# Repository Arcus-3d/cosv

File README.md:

## COSV - Cam Open Source Ventilator.
Cam based ventilator designed to fit directly on an BVM, on the patient.

The [COSV - Cam Open Source Ventilator](https://hackaday.io/project/170507) project is open source hardware. 
This github repository hosts the [OpenSCAD](http://www.openscad.org) source and the rendered STL images for quick access.

Hardware designs (schematics and CAD) files are licensed under the [GNU GENERAL PUBLIC LICENSE Version 3](https://www.gnu.org/licenses/gpl-3.0.md) and follow the terms of the [OSHW (Open-source hardware) Statement of Principles 1.0.](http://freedomdefined.org/OSHW)

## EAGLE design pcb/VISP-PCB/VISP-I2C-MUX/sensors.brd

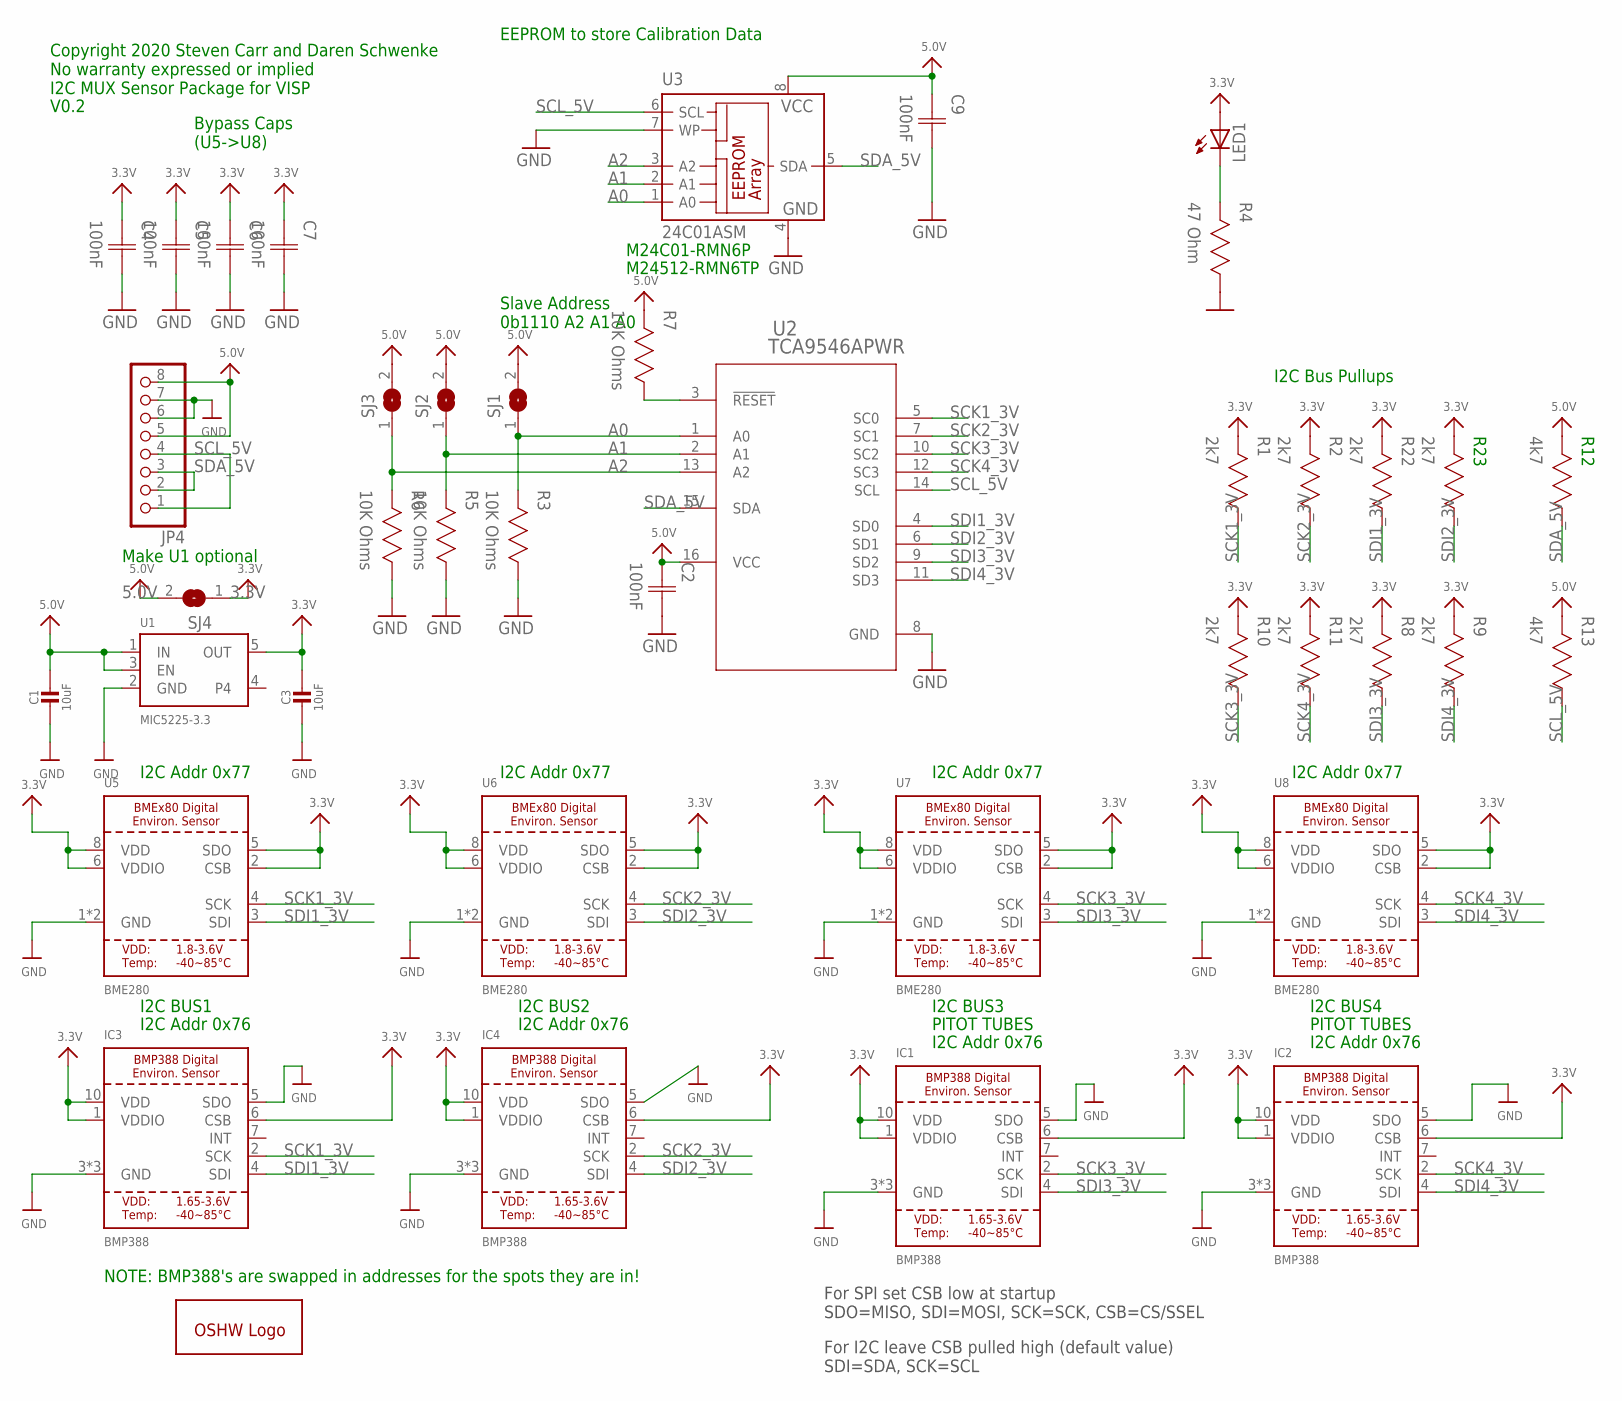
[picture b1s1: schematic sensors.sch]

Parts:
C1, C3: 10uF; _0805; MPN C1608X5R1A106M080AC
C2, C9: 100nF; CAP0402; MPN CL10B104KB8NNNC
C4, C5, C6, C7: 100nF; CAP0402; MPN CL10F104ZO8NNNC
GOLD_ORB_SM1: OSHWLOGOLOGO8MM; OSHW_8MM
IC1, IC2, IC3, IC4: BMP388; MPN BMP388
JP4: PINHD-1X08_2.54; 1X08
LED1: LEDCHIP-LED0603; CHIP-LED0603; MPN SML-D12P8WT86
R1, R2, R8, R9, R10, R11, R22, R23: 2k7; RES0402; MPN CRCW060310K0FKEAC
R3, R5, R6, R7: 10K Ohms; RES0402; MPN CRCW060310K0FKEAC
R4: 47 Ohm; RES0402; MPN RC0603FR-0747RL
R12, R13: 4k7; RES0402; MPN CRCW060310K0FKEAC
SJ1, SJ2, SJ3, SJ4: SJ
U1: MIC5225-3.3; SOT23-5; MPN MIC5225-3.3YM5-TR
U2: TCA9546APWR; PW16
U3: 24C01ASM; SO-08M; MPN M24C01-RMN6P
U5, U6, U7, U8: BME280

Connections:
3.3V: C3.1, C4.1 (C1), C5.1 (C1), C6.1 (C1), C7.1 (C1), IC1.1 (VDDIO), IC1.6 (CSB), IC1.10 (VDD), IC2.1 (VDDIO), IC2.6 (CSB), IC2.10 (VDD), IC3.1 (VDDIO), IC3.6 (CSB), IC3.10 (VDD), IC4.1 (VDDIO), IC4.6 (CSB), IC4.10 (VDD), LED1.A, R1.2, R2.2, R8.2, R9.2, R10.2, R11.2, R22.2, R23.2, SJ4.1, U1.5 (OUT), U5.2 (CSB), U5.5 (SDO), U5.6 (VDDIO), U5.8 (VDD), U6.2 (CSB), U6.5 (SDO), U6.6 (VDDIO), U6.8 (VDD), U7.2 (CSB), U7.5 (SDO), U7.6 (VDDIO), U7.8 (VDD), U8.2 (CSB), U8.5 (SDO), U8.6 (VDDIO), U8.8 (VDD)
5.0V: C1.1, C2.1 (C1), C9.1 (C1), JP4.5, JP4.8, R7.2, R12.2, R13.2, SJ1.2, SJ2.2, SJ3.2, SJ4.2, U1.1 (IN), U1.3 (EN), U2.16 (VCC), U3.8 (VCC)
A0: R3.2, SJ1.1, U2.1 (A0), U3.1 (A0)
A1: R5.2, SJ2.1, U2.2 (A1), U3.2 (A1)
A2: R6.2, SJ3.1, U2.13 (A2), U3.3 (A2)
GND: C1.2, C2.2 (C2), C3.2, C4.2 (C2), C5.2 (C2), C6.2 (C2), C7.2 (C2), C9.2 (C2), IC1.3 (GND), IC1.5 (SDO), IC1.8 (GND), IC1.9 (GND), IC2.3 (GND), IC2.5 (SDO), IC2.8 (GND), IC2.9 (GND), IC3.3 (GND), IC3.5 (SDO), IC3.8 (GND), IC3.9 (GND), IC4.3 (GND), IC4.5 (SDO), IC4.8 (GND), IC4.9 (GND), JP4.6, JP4.7, R3.1, R4.1, R5.1, R6.1, U1.2 (GND), U2.8 (GND), U3.4 (GND), U3.7 (WP), U5.1 (GND), U5.7 (GND), U6.1 (GND), U6.7 (GND), U7.1 (GND), U7.7 (GND), U8.1 (GND), U8.7 (GND)
LED: LED1.C, R4.2
RESET: R7.1, U2.3 (!RESET)
SCK1_3V: IC3.2 (SCK), R1.1, U2.5 (SC0), U5.4 (SCK)
SCK2_3V: IC4.2 (SCK), R2.1, U2.7 (SC1), U6.4 (SCK)
SCK3_3V: IC1.2 (SCK), R10.1, U2.10 (SC2), U7.4 (SCK)
SCK4_3V: IC2.2 (SCK), R11.1, U2.12 (SC3), U8.4 (SCK)
SCL_5V: JP4.1, JP4.4, R13.1, U2.14 (SCL), U3.6 (SCL)
SDA_5V: JP4.2, JP4.3, R12.1, U2.15 (SDA), U3.5 (SDA)
SDI1_3V: IC3.4 (SDI), R22.1, U2.4 (SD0), U5.3 (SDI)
SDI2_3V: IC4.4 (SDI), R23.1, U2.6 (SD1), U6.3 (SDI)
SDI3_3V: IC1.4 (SDI), R8.1, U2.9 (SD2), U7.3 (SDI)
SDI4_3V: IC2.4 (SDI), R9.1, U2.11 (SD3), U8.3 (SDI)

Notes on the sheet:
Bypass Caps (U5->U8)
Copyright 2020 Steven Carr and Daren Schwenke No warranty expressed or implied I2C MUX Sensor Package for VISP
EEPROM to store Calibration Data
V0.2
Make U1 optional
For SPI set CSB low at startup SDO=MISO, SDI=MOSI, SCK=SCK, CSB=CS/SSEL
For I2C leave CSB pulled high (default value) SDI=SDA, SCK=SCL
M24C01-RMN6P
M24512-RMN6TP
I2C Bus Pullups
Slave Address 0b1110 A2 A1 A0
I2C Addr 0x76
PITOT TUBES
I2C Addr 0x77
I2C BUS1
I2C BUS2
I2C BUS3
I2C BUS4
NOTE: BMP388's are swapped in addresses for the spots they are in!

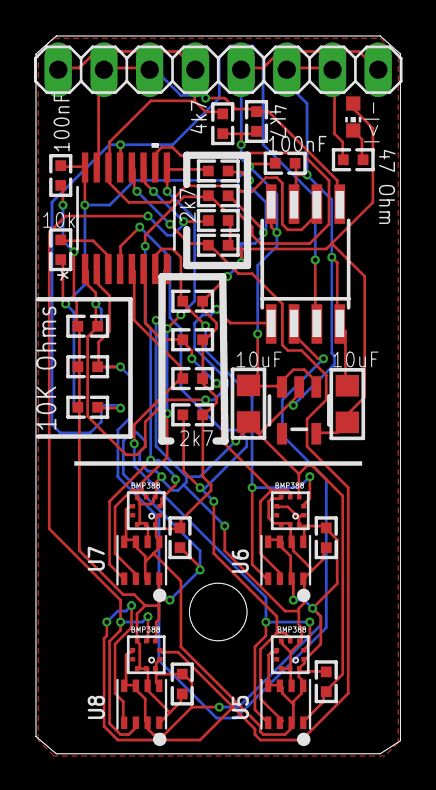
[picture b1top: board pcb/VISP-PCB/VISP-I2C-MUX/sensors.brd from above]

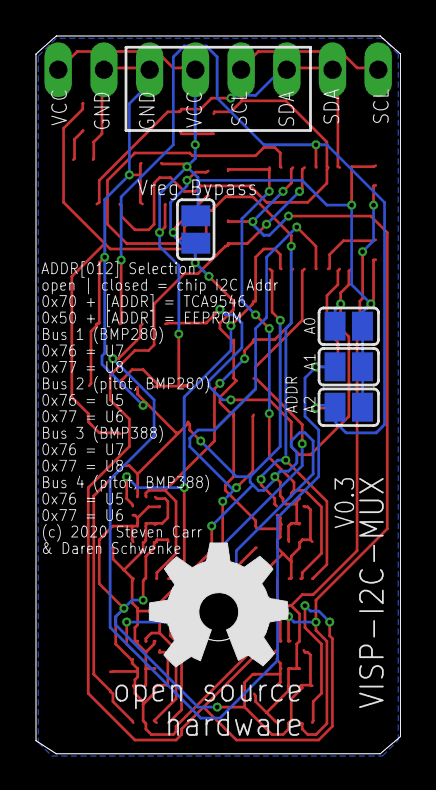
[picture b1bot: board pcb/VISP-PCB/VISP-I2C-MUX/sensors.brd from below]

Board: 2 copper layers, 20.2 x 39.9 mm, 41 parts (5 on the bottom side), 18 nets.

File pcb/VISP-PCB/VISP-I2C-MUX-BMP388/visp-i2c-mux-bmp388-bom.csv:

Item #,Qty,Ref Des,Manufacturer,Mfg Part #,Dist. Part #,Description,Package,Type
1,2,"C1,C3",Murata Electronics,GRM188R61A106KE69J ,490-14372-1-ND ,10uF ceramic capacitor,0805,SMT
2,6,"C2,C4,C5,C6,C7,C9",Murata Electronics, GRM155R71C104KA88J ,490-6328-1-ND ,100nF ceramic capacitor,0402,SMT
3,8,"R1,R2,R8,R9,R10,R11,R22,R23",TE Connectivity Passive Product,CRGCQ0402F2K7 ,A129632CT-ND ,2k7 resistor,0402,SMT
4,4,"R3,R5,R6,R7",TE Connectivity Passive Product,CRGCQ0402J10K ,A130054CT-ND ,10K resistor,0402,SMT
5,1,R4,TE Connectivity Passive Product,CRGCQ0402F47R , A129611CT-ND ,47 ohm resistor,0402,SMT
6,1,LED1,Rohm Semiconductor,SML-D12P8WT86,511-1579-1-ND ,LED GREEN DIFFUSED 0603 SMD ,0603,SMT
7,1,U1,Microchip Technology,MIC5225-3.3YM5-TR, 576-2980-1-ND ,IC REG LINEAR 3.3V 150MA SOT23-5 ,SOT23-5,SMT
8,1,U2,Texas Instruments,TCA9546APWR,296-40578-1-ND ,IC I2C SW 4CH W/RESET 16TSSOP ,16TSSOP,SMT
9,1,U3,Microchip Technology,AT24C512C-SSHD-T ,AT24C512C-SSHD-TCT-ND ,IC EEPROM 512K I2C 1MHZ 8SOIC ,SO-08M,SMT
10,4,"U5,U6,U7,U8",Bosch Sensortec,BMP388,828-1079-1-ND ,Barometric Pressure Sensor,BMP388,SMT
,,,,,,,,
,,,,,,,,
,,,,,,,,
Unique,10,,,,,,,
Total,29,,,,,,,
Thru Hole,0,,,,,,,
Has BGA,Yes,,,,,,,

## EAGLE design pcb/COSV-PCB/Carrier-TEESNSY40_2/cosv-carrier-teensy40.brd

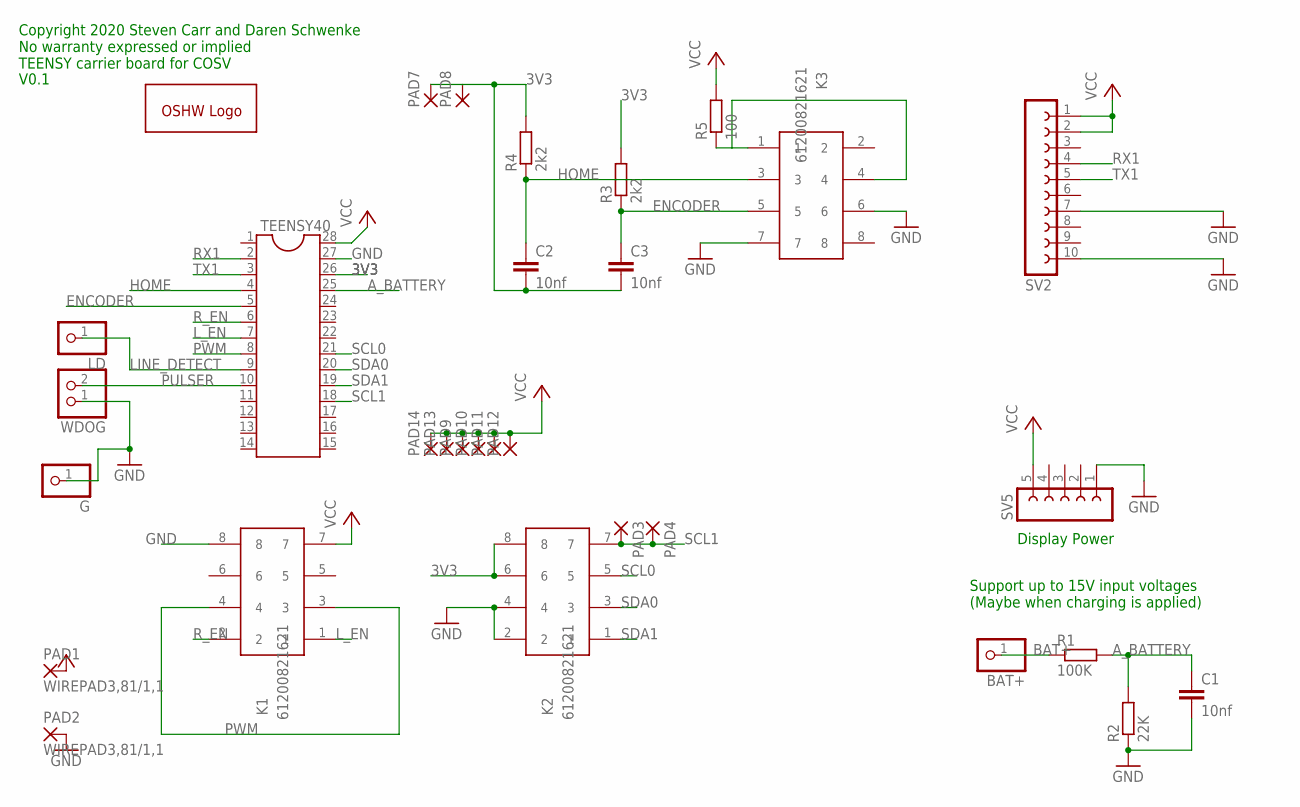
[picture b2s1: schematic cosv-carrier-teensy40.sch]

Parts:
BAT+: PINHD-1X01_2.54-S; 1X01-S
C1, C2, C3: 10nf; C1206
G: PINHD-1X01_2.54-S; 1X01-S
GOLD_ORB_SM1: OSHWLOGOLOGO8MM; OSHW_8MM
K1, K2, K3: 61200821621
LD: PINHD-1X01_2.54-S; 1X01-S
PAD1, PAD2: WIREPAD3,81/1,1; 3,81/1,1
PAD3, PAD4, PAD7, PAD8, PAD9, PAD10, PAD11, PAD12, PAD13, PAD14: 1,6/0,9
R1: 100K; R1206
R2: 22K; R1206
R3, R4: 2k2; R1206
R5: 100; R1206
SV2: FE10-1; FE10
SV5: FE05W
TEENSY40: DIL28; DIL28-6
WDOG: PINHD-1X2; 1X02

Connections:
3V3: C2.2, C3.2, K2.6, K2.8, PAD7.1, PAD8.1, R3.2, R4.2, TEENSY40.26
A_BATTERY: C1.1, R1.2, R2.2, TEENSY40.25
BAT+: BAT+.1, R1.1
ENCODER: C3.1, K3.5, R3.1, TEENSY40.5
GND: C1.2, G.1, K1.8, K2.2, K2.4, K3.6, K3.7, PAD2.1, R2.1, SV2.7, SV2.10, SV5.1, TEENSY40.27, WDOG.1
HOME: C2.1, K3.3, R4.1, TEENSY40.4
LED: K3.1, K3.4, R5.1
LINE_DETECT: LD.1, TEENSY40.9
L_EN: K1.1, TEENSY40.7
PULSER: TEENSY40.10, WDOG.2
PWM: K1.3, K1.4, TEENSY40.8
RX1: SV2.4, TEENSY40.2
R_EN: K1.2, TEENSY40.6
SCL0: K2.5, TEENSY40.21
SCL1: K2.7, PAD3.1, PAD4.1, TEENSY40.18
SDA0: K2.3, TEENSY40.20
SDA1: K2.1, TEENSY40.19
TX1: SV2.5, TEENSY40.3
VCC: K1.7, PAD1.1, PAD9.1, PAD10.1, PAD11.1, PAD12.1, PAD13.1, PAD14.1, R5.2, SV2.1, SV2.2, SV5.5, TEENSY40.28

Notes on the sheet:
Display Power
Support up to 15V input voltages (Maybe when charging is applied)
Copyright 2020 Steven Carr and Daren Schwenke No warranty expressed or implied TEENSY carrier board for COSV
V0.1

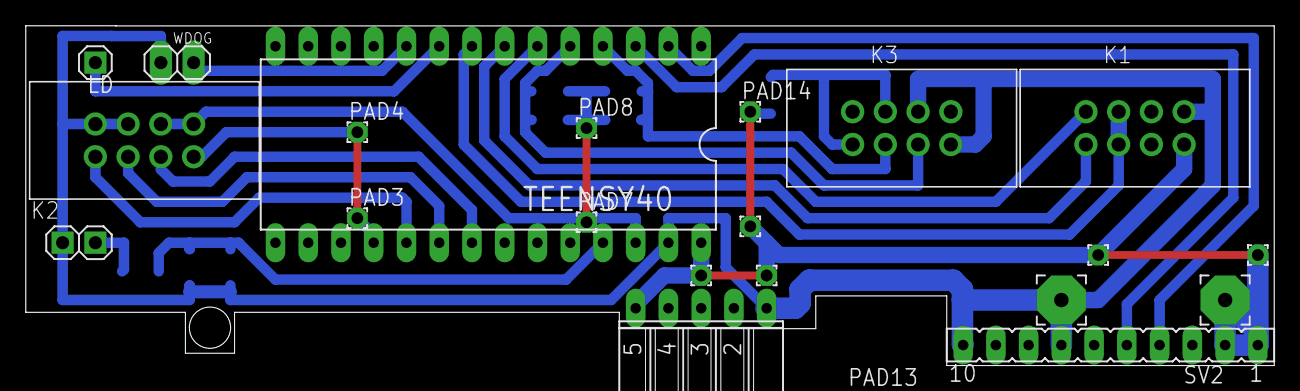
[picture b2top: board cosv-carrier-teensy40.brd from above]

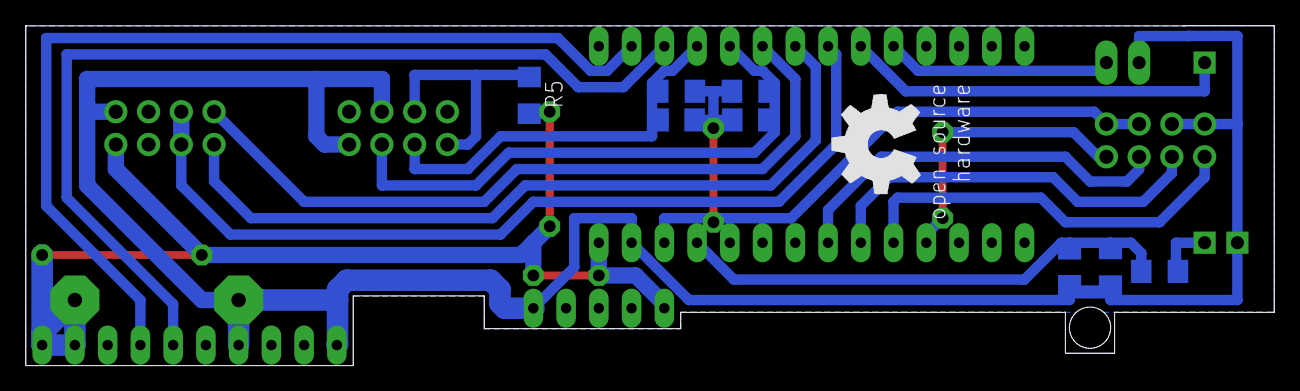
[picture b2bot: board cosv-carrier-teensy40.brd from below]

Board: 2 copper layers, 96.8 x 26.4 mm, 31 parts (9 on the bottom side), 19 nets.

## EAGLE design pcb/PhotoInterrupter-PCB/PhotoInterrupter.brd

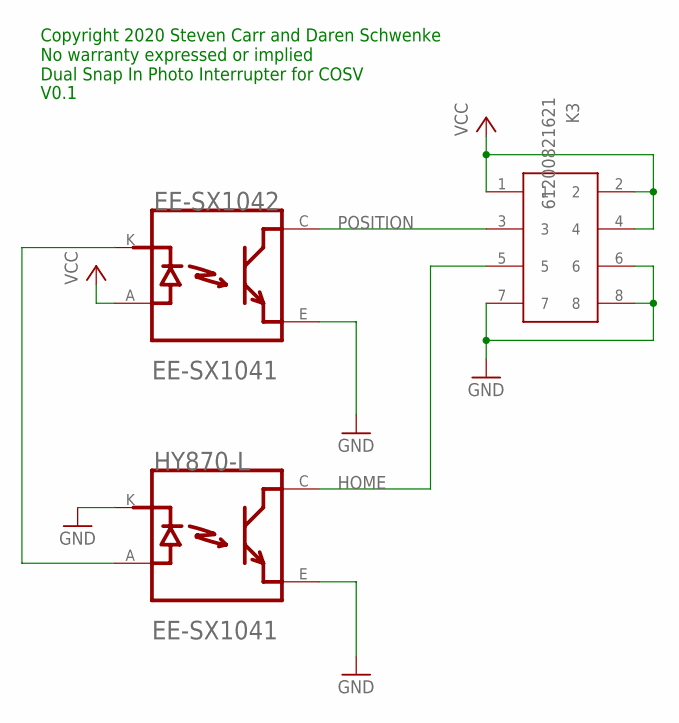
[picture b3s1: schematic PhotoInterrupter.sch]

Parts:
EE-SX1042: OMRON_ELECTRONICS_INC-EMC_DIV_EE-SX1041OMRON_ELEC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; OMRON_ELECTRONICS_INC-EMC_DIV_EE-SX1041_0
HY870-L: OMRON_ELECTRONICS_INC-EMC_DIV_EE-SX1041OMRON_ELEC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; OMRON_ELECTRONICS_INC-EMC_DIV_EE-SX1041_0
K3: 61200821621

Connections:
GND: EE-SX1042.E, HY870-L.E, HY870-L.K, K3.6, K3.7, K3.8
HOME: HY870-L.C, K3.5
unnamed: EE-SX1042.K, HY870-L.A
POSITION: EE-SX1042.C, K3.3
VCC: EE-SX1042.A, K3.1, K3.2, K3.4

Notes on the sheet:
Copyright 2020 Steven Carr and Daren Schwenke No warranty expressed or implied Dual Snap In Photo Interrupter for COSV
V0.1

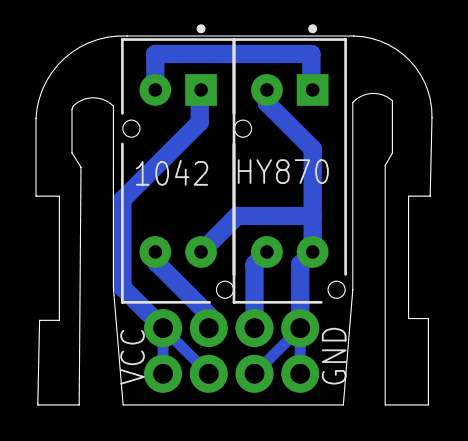
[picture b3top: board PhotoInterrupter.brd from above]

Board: 2 copper layers, 22.0 x 20.5 mm, 3 parts (1 on the bottom side), 5 nets.

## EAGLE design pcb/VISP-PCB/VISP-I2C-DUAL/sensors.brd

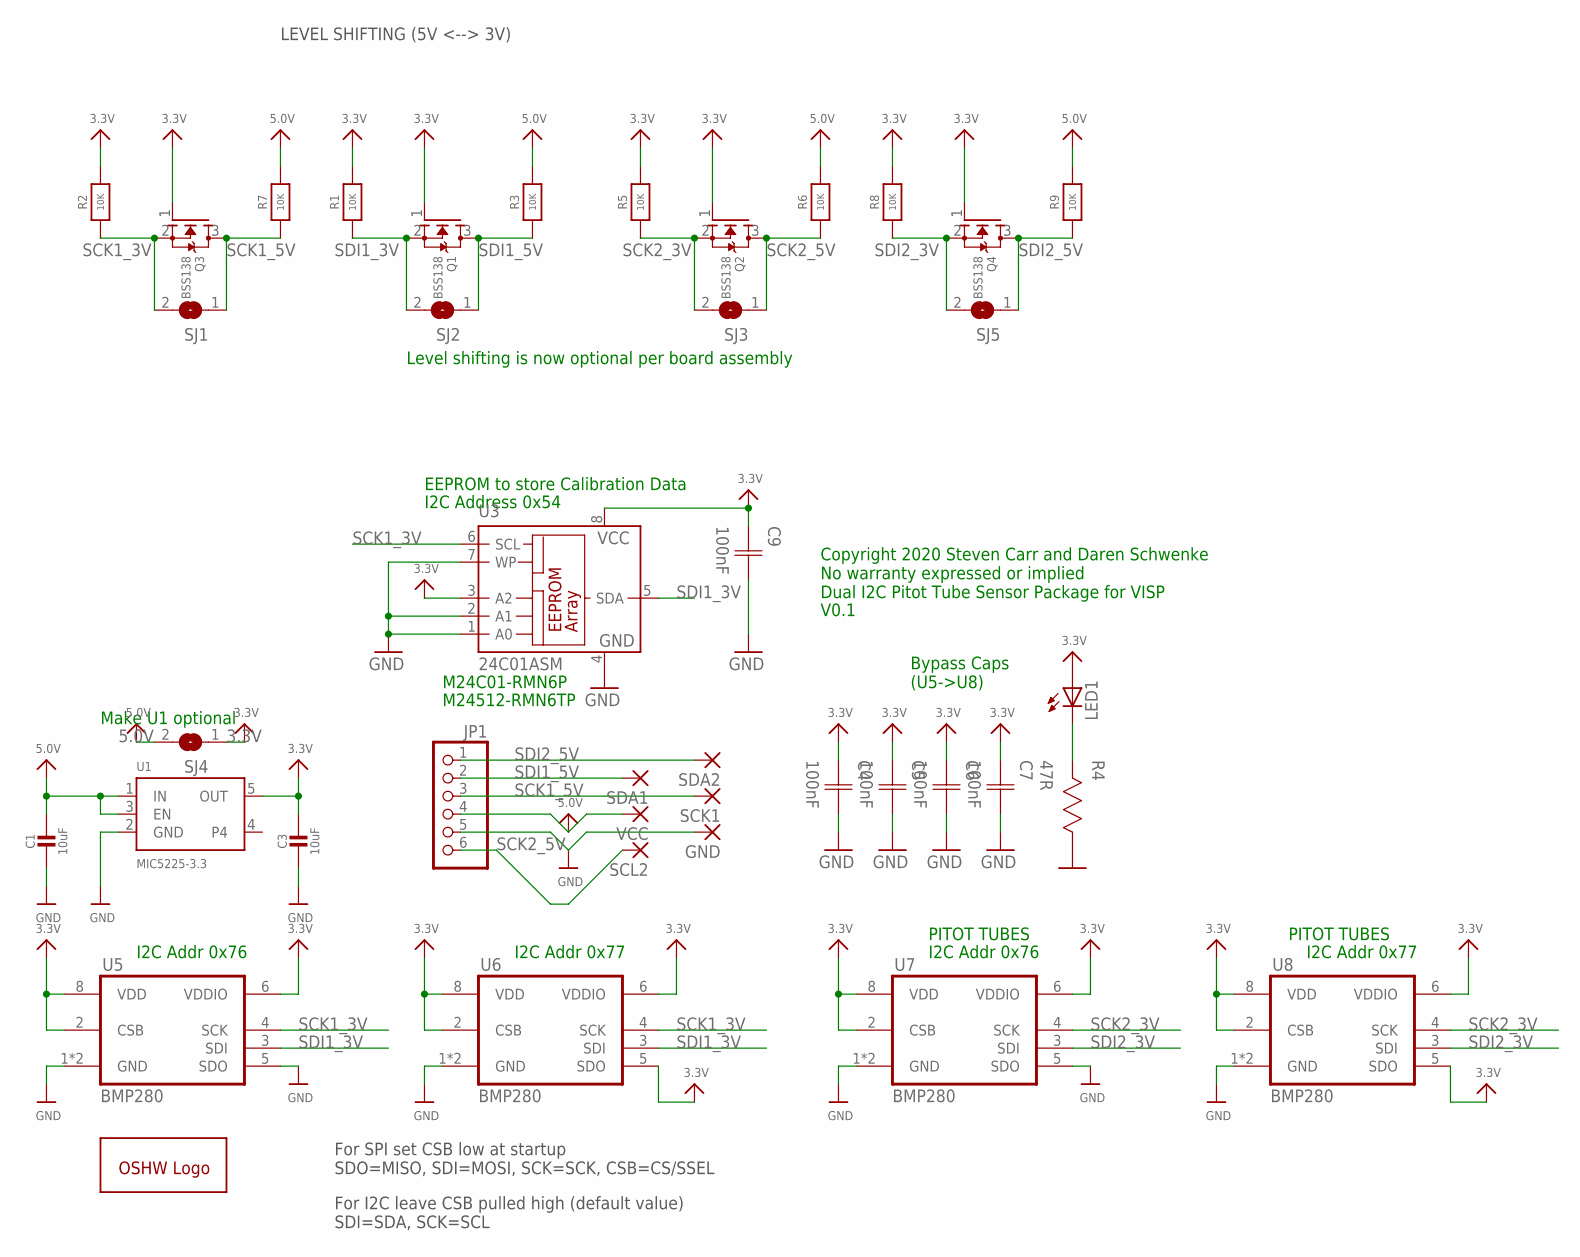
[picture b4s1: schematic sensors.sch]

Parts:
C1, C3: 10uF; _0805; MPN C1608X5R1A106M080AC
C4, C5, C6, C7: 100nF; CAP0402; MPN CL10F104ZO8NNNC
C9: 100nF; CAP0402; MPN CL10B104KB8NNNC
GND: SMD2; SMD1,27-2,54
GOLD_ORB_SM1: OSHWLOGOLOGO8MM; OSHW_8MM
JP1: PINHD-1X6; 1X06
LED1: LEDCHIP-LED0603; CHIP-LED0603; MPN SML-D12P8WT86
Q1, Q2, Q3, Q4: BSS138; SOT23-WIDE
R1, R2, R3, R5, R6, R7, R8, R9: 10K; _0402
R4: 47R; RES0402; MPN RC0603FR-0747RL
SCK1: SMD2; SMD1,27-2,54
SCL2: SMD2; SMD1,27-2,54
SDA1, SDA2: SMD2; SMD1,27-2,54
SJ1, SJ2, SJ3, SJ4, SJ5: SJ
U1: MIC5225-3.3; SOT23-5; MPN MIC5225-3.3YM5-TR
U3: 24C01ASM; SO-08M; MPN M24C01-RMN6P
U5, U6, U7, U8: BMP280; MPN BMP280
VCC: SMD2; SMD1,27-2,54

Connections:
3.3V: C3.1, C4.1 (C1), C5.1 (C1), C6.1 (C1), C7.1 (C1), C9.1 (C1), LED1.A, Q1.1 (G), Q2.1 (G), Q3.1 (G), Q4.1 (G), R1.2, R2.2, R5.2, R8.2, SJ4.1, U1.5 (OUT), U3.3 (A2), U3.8 (VCC), U5.2 (CSB), U5.6 (VDDIO), U5.8 (VDD), U6.2 (CSB), U6.5 (SDO), U6.6 (VDDIO), U6.8 (VDD), U7.2 (CSB), U7.6 (VDDIO), U7.8 (VDD), U8.2 (CSB), U8.5 (SDO), U8.6 (VDDIO), U8.8 (VDD)
5.0V: C1.1, JP1.4, R3.2, R6.2, R7.2, R9.2, SJ4.2, U1.1 (IN), U1.3 (EN), VCC.1
GND: C1.2, C3.2, C4.2 (C2), C5.2 (C2), C6.2 (C2), C7.2 (C2), C9.2 (C2), GND.1, JP1.5, R4.1, U1.2 (GND), U3.1 (A0), U3.2 (A1), U3.4 (GND), U3.7 (WP), U5.1 (GND), U5.5 (SDO), U5.7 (GND), U6.1 (GND), U6.7 (GND), U7.1 (GND), U7.5 (SDO), U7.7 (GND), U8.1 (GND), U8.7 (GND)
LED: LED1.C, R4.2
SCK1_3V: Q3.2 (S), R2.1, SJ1.2, U3.6 (SCL), U5.4 (SCK), U6.4 (SCK)
SCK1_5V: JP1.3, Q3.3 (D), R7.1, SCK1.1, SJ1.1
SCK2_3V: Q2.2 (S), R5.1, SJ3.2, U7.4 (SCK), U8.4 (SCK)
SCK2_5V: JP1.6, Q2.3 (D), R6.1, SCL2.1, SJ3.1
SDI1_3V: Q1.2 (S), R1.1, SJ2.2, U3.5 (SDA), U5.3 (SDI), U6.3 (SDI)
SDI1_5V: JP1.2, Q1.3 (D), R3.1, SDA1.1, SJ2.1
SDI2_3V: Q4.2 (S), R8.1, SJ5.2, U7.3 (SDI), U8.3 (SDI)
SDI2_5V: JP1.1, Q4.3 (D), R9.1, SDA2.1, SJ5.1

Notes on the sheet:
Bypass Caps (U5->U8)
Copyright 2020 Steven Carr and Daren Schwenke No warranty expressed or implied Dual I2C Pitot Tube Sensor Package for VISP
I2C Addr 0x76
I2C Addr 0x77
V0.1
Make U1 optional
PITOT TUBES
For SPI set CSB low at startup SDO=MISO, SDI=MOSI, SCK=SCK, CSB=CS/SSEL
For I2C leave CSB pulled high (default value) SDI=SDA, SCK=SCL
EEPROM to store Calibration Data
M24C01-RMN6P
M24512-RMN6TP
I2C Address 0x54
LEVEL SHIFTING (5V <--> 3V)
Level shifting is now optional per board assembly

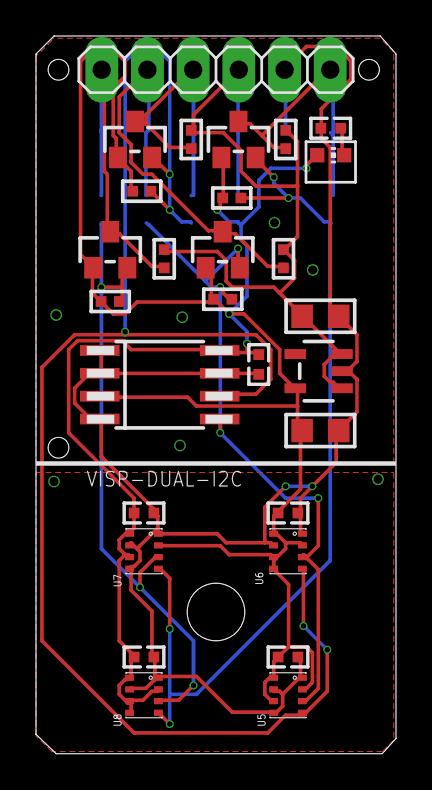
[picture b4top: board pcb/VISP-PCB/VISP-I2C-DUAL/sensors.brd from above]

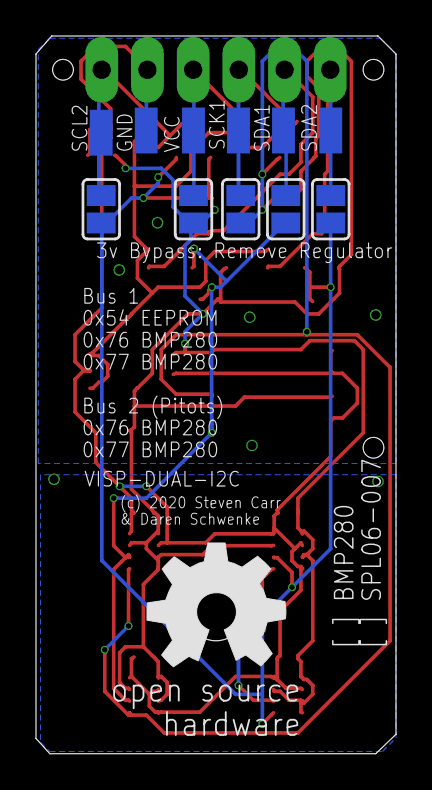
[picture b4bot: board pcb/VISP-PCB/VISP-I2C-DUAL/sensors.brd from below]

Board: 2 copper layers, 20.0 x 39.9 mm, 40 parts (12 on the bottom side), 12 nets.

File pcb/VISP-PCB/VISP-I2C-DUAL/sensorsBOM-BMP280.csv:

Qty,Designator,Footprint,Comment,LCSC Part # (optional),Description (optional)
2,"C1,C3",C0805,10uF ±10% 10V,C15850,10uF ±10% 10V B 0805 Multilayer Ceramic Capacitors MLCC - SMD/SMT RoHS
5,"C4,C5,C6,C7,C9",C0402,100nF ±10% 50V X7R,C1525,
4,"Q1,Q2,Q3,Q4",SOT-23-3,BSS138,C78284,"N Channel 50V 220mA 1.5V @ 1mA 3.5 Ω @ 220mA,10V 360mW SOT-23(SOT-23-3) MOSFET RoHS"
8,"R1,R2,R3,R5,R6,R7,R8,R9",R0402,10K ±1% 1/16W,C25744,10K ±1% 1/16W 0402 Chip Resistor - Surface Mount RoHS
1,R4,R0402,47K ±1% 1/16W,C25792,47K ±1% 1/16W 0402 Chip Resistor - Surface Mount RoHS
1,LED1,LED_0603,Light Emitting Diodes (LED) Green 520~535nm 112~258mcd@20mA,C72043,Light Emitting Diodes (LED) Green 520~535nm 112~258mcd@20mA
1,U1,SOT-23-5,BL9198-33BAPRN,C51282,Fixed 6V 3.3V 300mA SOT-23-5 Low Dropout Regulators(LDO) RoHS
1,U3,SO-8,M24C01-RMN6TP,C146163,SO-8 EEPROM RoHS
4,"U5,U6,U7,U8",LGA-8,BMP280,C83291,LGA-8 Gas Sensors RoHS

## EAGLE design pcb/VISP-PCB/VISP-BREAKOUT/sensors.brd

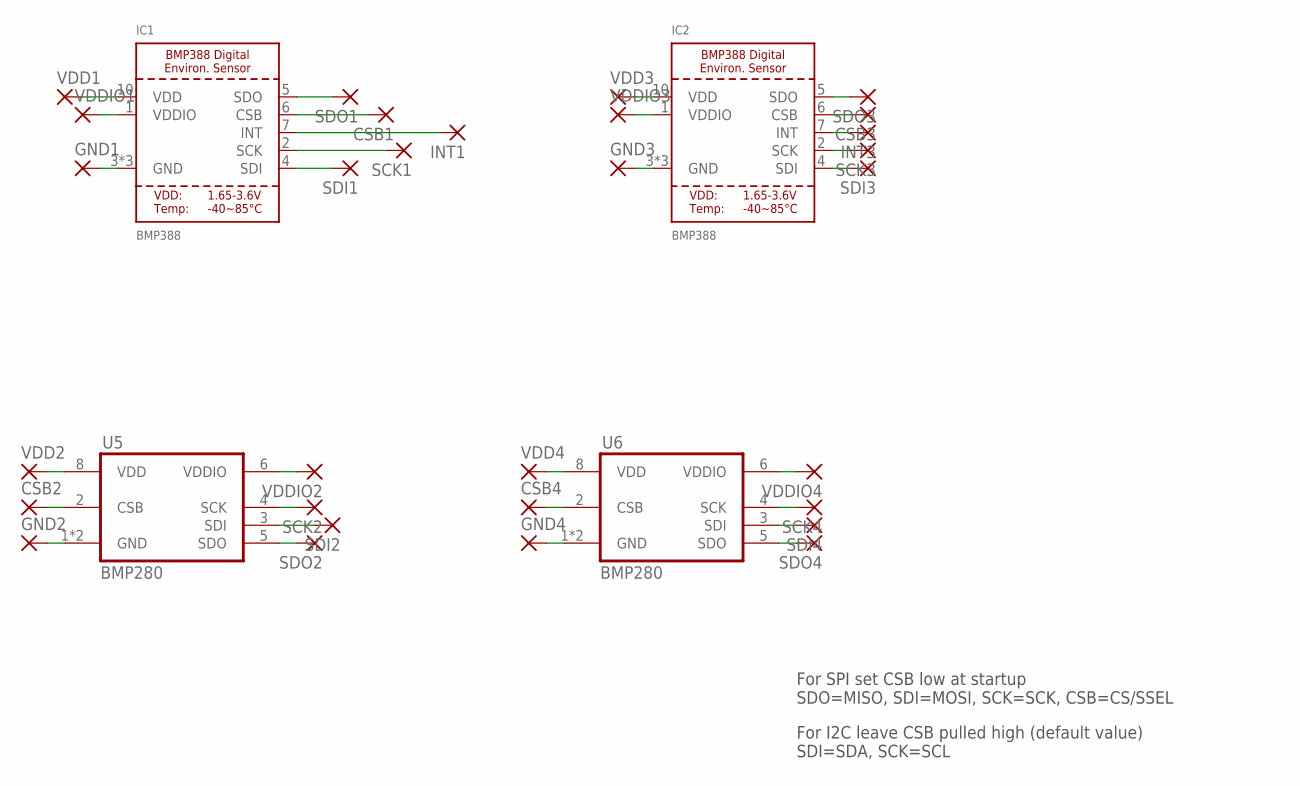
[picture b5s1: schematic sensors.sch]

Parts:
CSB1, CSB2, CSB3, CSB4: SMD5; SMD2,54-5,08
GND1, GND2, GND3, GND4: SMD5; SMD2,54-5,08
IC1, IC2: BMP388; MPN BMP388
INT1, INT3: SMD5; SMD2,54-5,08
SCK1, SCK2, SCK3, SCK4: SMD5; SMD2,54-5,08
SDI1, SDI2, SDI3, SDI4: SMD5; SMD2,54-5,08
SDO1, SDO2, SDO3, SDO4: SMD5; SMD2,54-5,08
U5, U6: BMP280; MPN BMP280
VDD1, VDD2, VDD3, VDD4: SMD5; SMD2,54-5,08
VDDIO1, VDDIO2, VDDIO3, VDDIO4: SMD5; SMD2,54-5,08

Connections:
unnamed: IC1.10 (VDD), VDD1.1
unnamed: IC1.1 (VDDIO), VDDIO1.1
unnamed: GND1.1, IC1.3 (GND), IC1.8 (GND), IC1.9 (GND)
unnamed: IC1.5 (SDO), SDO1.1
unnamed: CSB1.1, IC1.6 (CSB)
unnamed: IC1.7 (INT), INT1.1
unnamed: IC1.2 (SCK), SCK1.1
unnamed: IC1.4 (SDI), SDI1.1
unnamed: U5.8 (VDD), VDD2.1
unnamed: CSB2.1, U5.2 (CSB)
unnamed: GND2.1, U5.1 (GND), U5.7 (GND)
unnamed: U5.6 (VDDIO), VDDIO2.1
unnamed: SCK2.1, U5.4 (SCK)
unnamed: SDI2.1, U5.3 (SDI)
unnamed: SDO2.1, U5.5 (SDO)
unnamed: IC2.10 (VDD), VDD3.1
unnamed: IC2.1 (VDDIO), VDDIO3.1
unnamed: GND3.1, IC2.3 (GND), IC2.8 (GND), IC2.9 (GND)
unnamed: IC2.5 (SDO), SDO3.1
unnamed: CSB3.1, IC2.6 (CSB)
unnamed: IC2.7 (INT), INT3.1
unnamed: IC2.2 (SCK), SCK3.1
unnamed: IC2.4 (SDI), SDI3.1
unnamed: U6.6 (VDDIO), VDDIO4.1
unnamed: SCK4.1, U6.4 (SCK)
unnamed: SDI4.1, U6.3 (SDI)
unnamed: SDO4.1, U6.5 (SDO)
unnamed: GND4.1, U6.1 (GND), U6.7 (GND)
unnamed: CSB4.1, U6.2 (CSB)
unnamed: U6.8 (VDD), VDD4.1

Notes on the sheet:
For SPI set CSB low at startup SDO=MISO, SDI=MOSI, SCK=SCK, CSB=CS/SSEL
For I2C leave CSB pulled high (default value) SDI=SDA, SCK=SCL

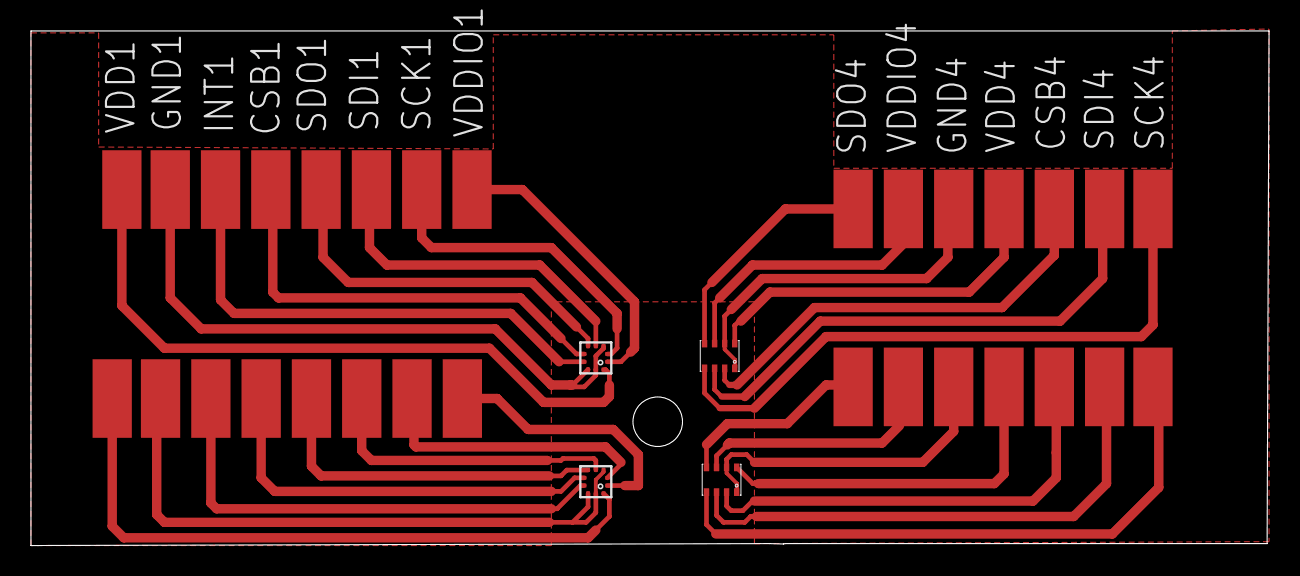
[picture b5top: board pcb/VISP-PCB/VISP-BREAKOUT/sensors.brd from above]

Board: 2 copper layers, 80.0 x 33.2 mm, 34 parts (0 on the bottom side), 30 nets.

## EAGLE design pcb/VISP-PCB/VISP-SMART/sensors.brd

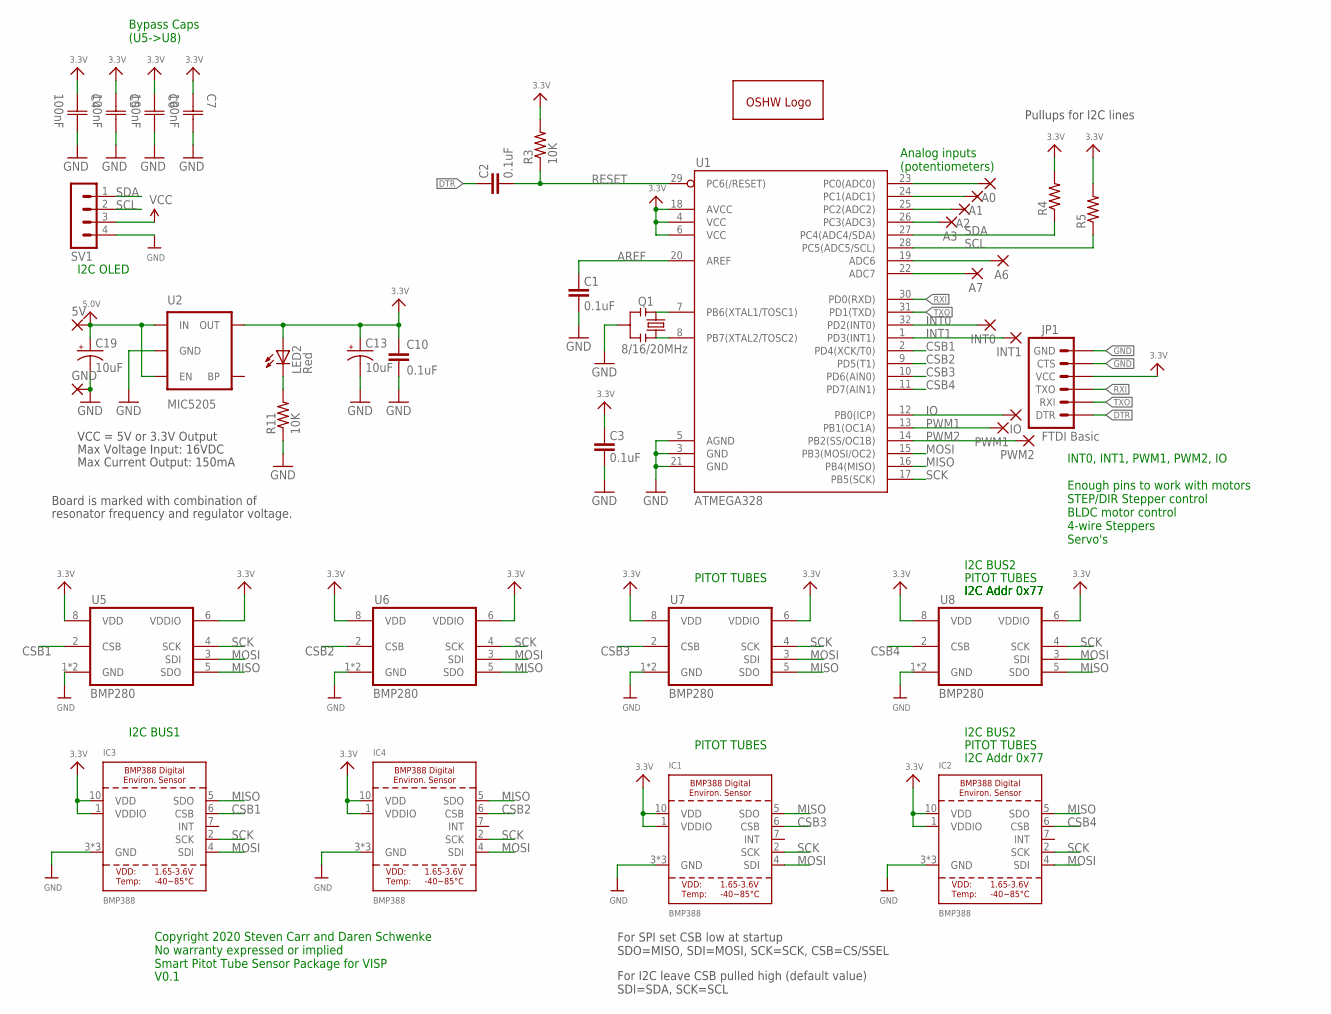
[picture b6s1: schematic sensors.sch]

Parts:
5V: SMD2; SMD1,27-2,54
A0, A1, A2, A3, A6, A7: SMD2; SMD1,27-2,54
C1, C2, C3, C10: 0.1uF; 0603-CAP
C4, C5, C6, C7: 100nF; CAP0402; MPN CL10F104ZO8NNNC
C13, C19: 10uF; EIA3216
GND: SMD2; SMD1,27-2,54
GOLD_ORB_SM1: OSHWLOGOLOGO8MM; OSHW_8MM
IC1, IC2, IC3, IC4: BMP388; MPN BMP388
INT0, INT1: SMD2; SMD1,27-2,54
IO: SMD2; SMD1,27-2,54
JP1: FTDI Basic; 1X06
LED2: Red; 0603-LED-ALT1
PWM1, PWM2: SMD2; SMD1,27-2,54
Q1: 8/16/20MHz; RESONATOR-SMD-1:1
R3, R11: 10K; 0603-RES
R4, R5: RESISTOR0603-RES; 0603-RES
SV1: MA04-1
U1: ATMEGA328; TQFP32-08
U2: MIC5205; SOT23-5
U5, U6, U7, U8: BMP280; MPN BMP280

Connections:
3.3V: C3.2, C4.1 (C1), C5.1 (C1), C6.1 (C1), C7.1 (C1), C10.1, C13.A (+), IC1.1 (VDDIO), IC1.10 (VDD), IC2.1 (VDDIO), IC2.10 (VDD), IC3.1 (VDDIO), IC3.10 (VDD), IC4.1 (VDDIO), IC4.10 (VDD), JP1.4 (VCC), LED2.A, R3.2, R4.2, R5.2, SV1.3, U1.4 (VCC), U1.6 (VCC), U1.18 (AVCC), U2.5 (OUT), U5.6 (VDDIO), U5.8 (VDD), U6.6 (VDDIO), U6.8 (VDD), U7.6 (VDDIO), U7.8 (VDD), U8.6 (VDDIO), U8.8 (VDD)
5.0V: 5V.1, C19.A (+), U2.1 (IN), U2.3 (EN)
A0: A0.1, U1.23 (PC0(ADC0))
A1: A1.1, U1.24 (PC1(ADC1))
A2: A2.1, U1.25 (PC2(ADC2))
A3: A3.1, U1.26 (PC3(ADC3))
A6: A6.1, U1.19 (ADC6)
A7: A7.1, U1.22 (ADC7)
AREF: C1.2, U1.20 (AREF)
CSB1: IC3.6 (CSB), U1.2 (PD4(XCK/T0)), U5.2 (CSB)
CSB2: IC4.6 (CSB), U1.9 (PD5(T1)), U6.2 (CSB)
CSB3: IC1.6 (CSB), U1.10 (PD6(AIN0)), U7.2 (CSB)
CSB4: IC2.6 (CSB), U1.11 (PD7(AIN1)), U8.2 (CSB)
DTR: C2.2, JP1.1 (DTR)
GND: C1.1, C3.1, C4.2 (C2), C5.2 (C2), C6.2 (C2), C7.2 (C2), C10.2, C13.C (-), C19.C (-), GND.1, IC1.3 (GND), IC1.8 (GND), IC1.9 (GND), IC2.3 (GND), IC2.8 (GND), IC2.9 (GND), IC3.3 (GND), IC3.8 (GND), IC3.9 (GND), IC4.3 (GND), IC4.8 (GND), IC4.9 (GND), JP1.5 (CTS), JP1.6 (GND), Q1.2, R11.1, SV1.4, U1.3 (GND), U1.5 (AGND), U1.21 (GND), U2.2 (GND), U5.1 (GND), U5.7 (GND), U6.1 (GND), U6.7 (GND), U7.1 (GND), U7.7 (GND), U8.1 (GND), U8.7 (GND)
INT0: INT0.1, U1.32 (PD2(INT0))
INT1: INT1.1, U1.1 (PD3(INT1))
IO: IO.1, U1.12 (PB0(ICP))
MISO: IC1.5 (SDO), IC2.5 (SDO), IC3.5 (SDO), IC4.5 (SDO), U1.16 (PB4(MISO)), U5.5 (SDO), U6.5 (SDO), U7.5 (SDO), U8.5 (SDO)
MOSI: IC1.4 (SDI), IC2.4 (SDI), IC3.4 (SDI), IC4.4 (SDI), U1.15 (PB3(MOSI/OC2)), U5.3 (SDI), U6.3 (SDI), U7.3 (SDI), U8.3 (SDI)
unnamed: Q1.3, U1.8 (PB7(XTAL2/TOSC2))
unnamed: Q1.1, U1.7 (PB6(XTAL1/TOSC1))
unnamed: LED2.C, R11.2
PWM1: PWM1.1, U1.13 (PB1(OC1A))
PWM2: PWM2.1, U1.14 (PB2(SS/OC1B))
RESET: C2.1, R3.1, U1.29 (PC6(/RESET))
RXI: JP1.3 (TXO), U1.30 (PD0(RXD))
SCK: IC1.2 (SCK), IC2.2 (SCK), IC3.2 (SCK), IC4.2 (SCK), U1.17 (PB5(SCK)), U5.4 (SCK), U6.4 (SCK), U7.4 (SCK), U8.4 (SCK)
SCL: R5.1, SV1.2, U1.28 (PC5(ADC5/SCL))
SDA: R4.1, SV1.1, U1.27 (PC4(ADC4/SDA))
TXO: JP1.2 (RXI), U1.31 (PD1(TXD))

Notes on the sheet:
Bypass Caps (U5->U8)
Copyright 2020 Steven Carr and Daren Schwenke No warranty expressed or implied Smart Pitot Tube Sensor Package for VISP
I2C Addr 0x77
V0.1
PITOT TUBES
For SPI set CSB low at startup SDO=MISO, SDI=MOSI, SCK=SCK, CSB=CS/SSEL
For I2C leave CSB pulled high (default value) SDI=SDA, SCK=SCL
I2C BUS1
I2C BUS2
Max Voltage Input: 16VDC
Max Current Output: 150mA
Board is marked with combination of
resonator frequency and regulator voltage.
VCC = 5V or 3.3V Output
Pullups for I2C lines
I2C OLED
Analog inputs (potentiometers)
INT0, INT1, PWM1, PWM2, IO Enough pins to work with motors STEP/DIR Stepper control BLDC motor control 4-wire Steppers Servo's

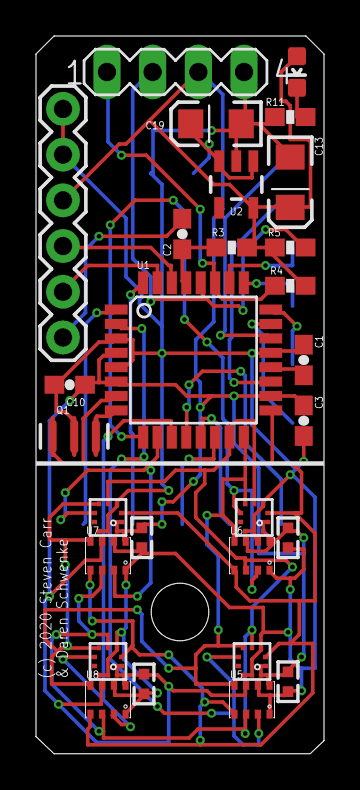
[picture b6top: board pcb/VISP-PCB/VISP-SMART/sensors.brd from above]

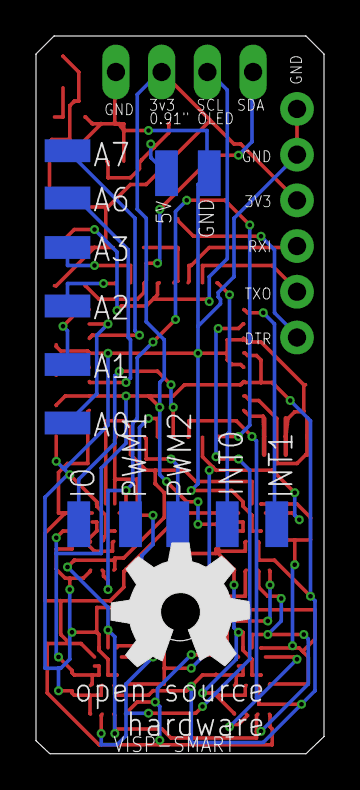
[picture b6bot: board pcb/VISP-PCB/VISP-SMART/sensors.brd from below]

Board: 2 copper layers, 16.0 x 39.9 mm, 42 parts (14 on the bottom side), 31 nets.

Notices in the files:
pcb/COSV-PCB/Carrier-TEESNSY40_2/cosv-carrier-teensy40.brd:
(c) 2020 Steven Carr and Daren Schwenke
parts and their libraries:
Wuerth_Elektronik_eiCan_05_Box_Header_ID: Copyright: Würth Elektronik
